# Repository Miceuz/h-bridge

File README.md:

h-bridge
========

High voltage H-bridge driver

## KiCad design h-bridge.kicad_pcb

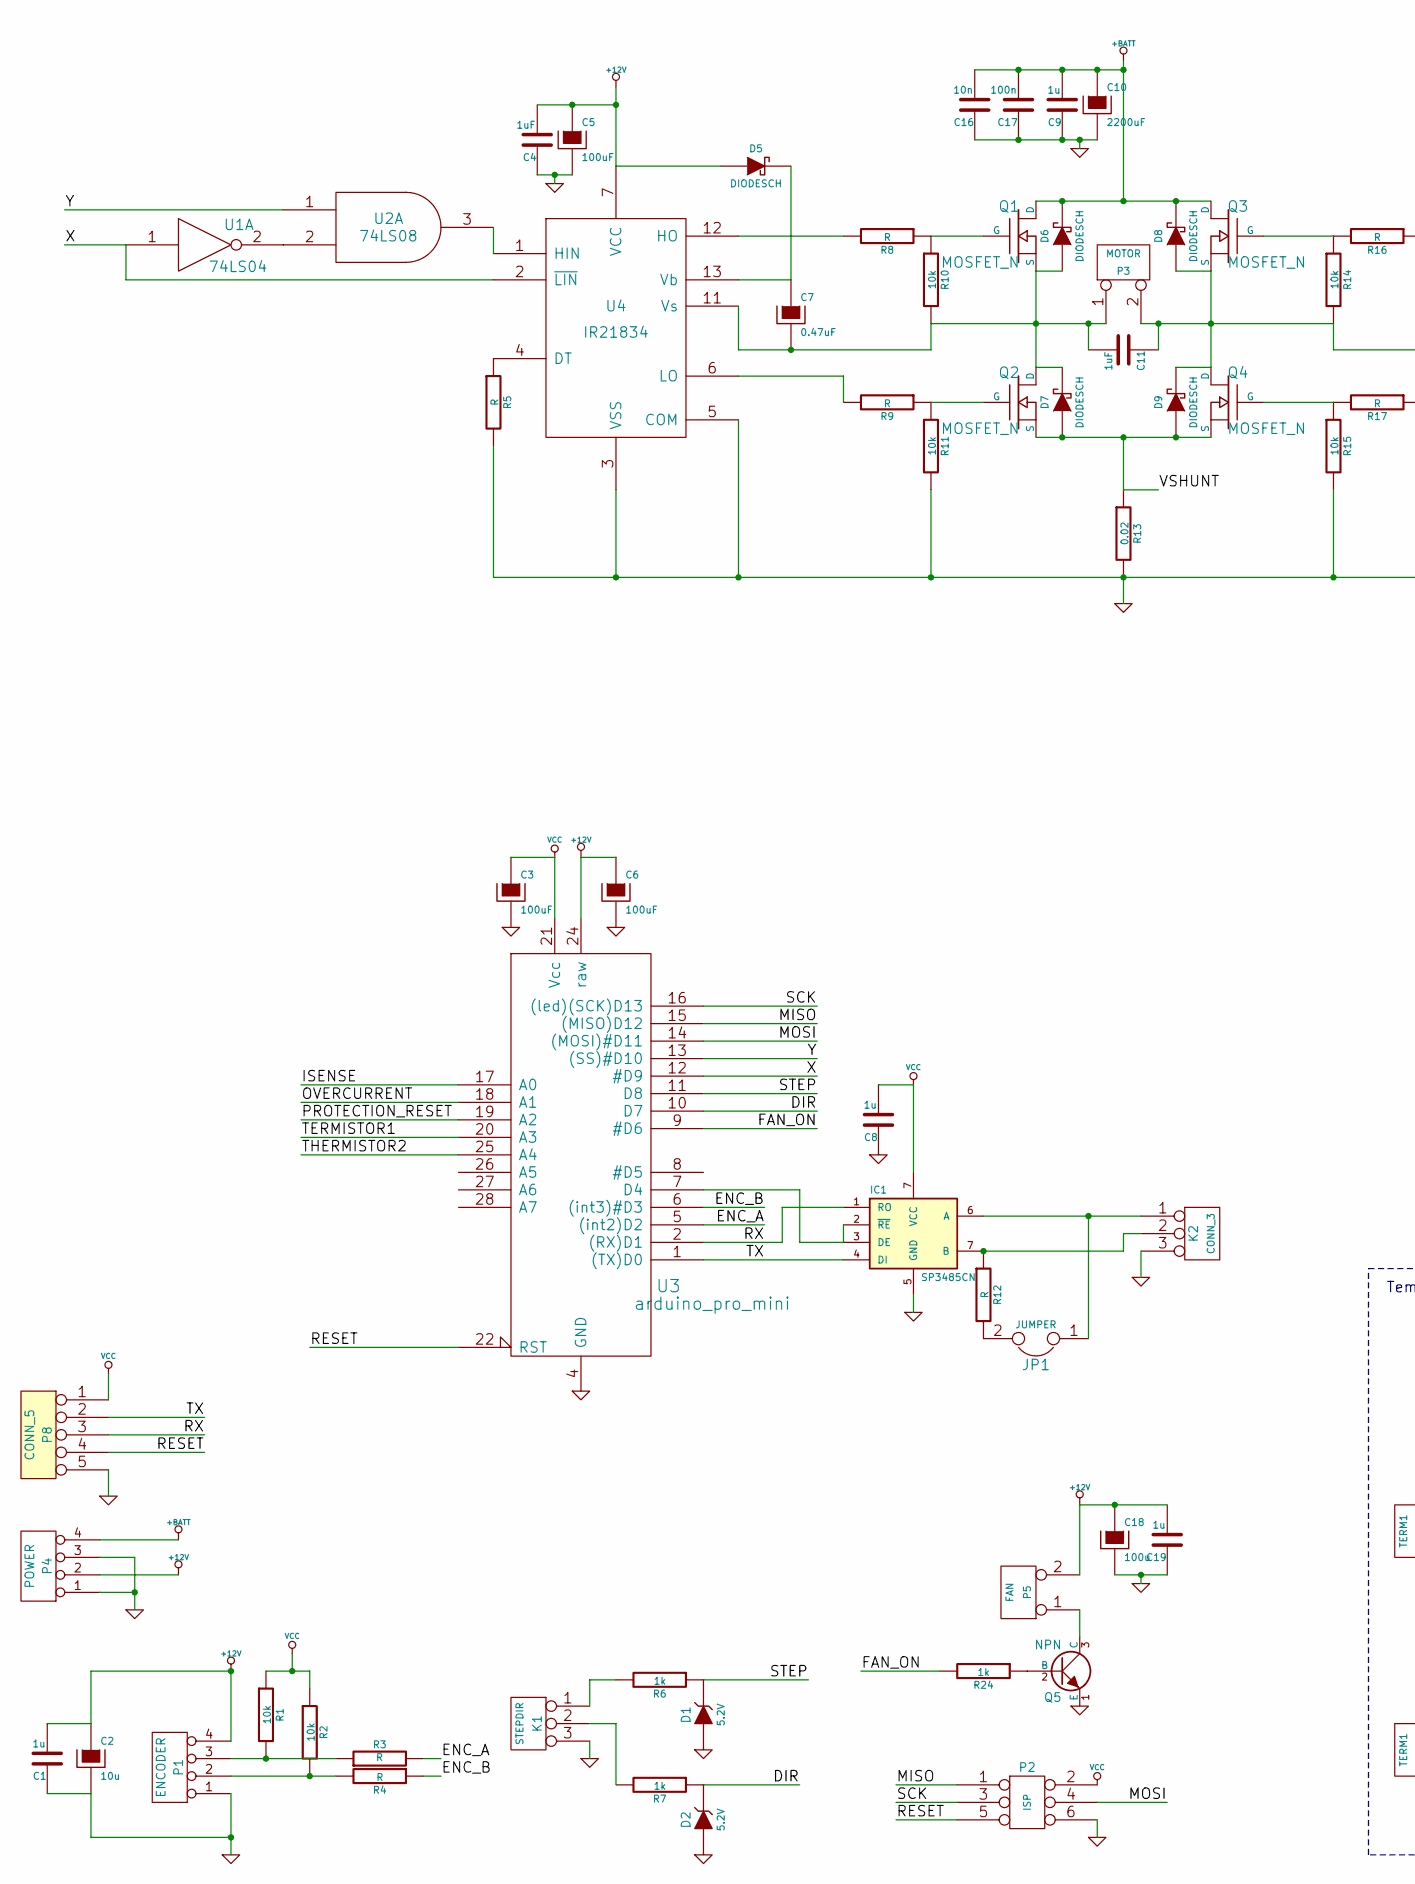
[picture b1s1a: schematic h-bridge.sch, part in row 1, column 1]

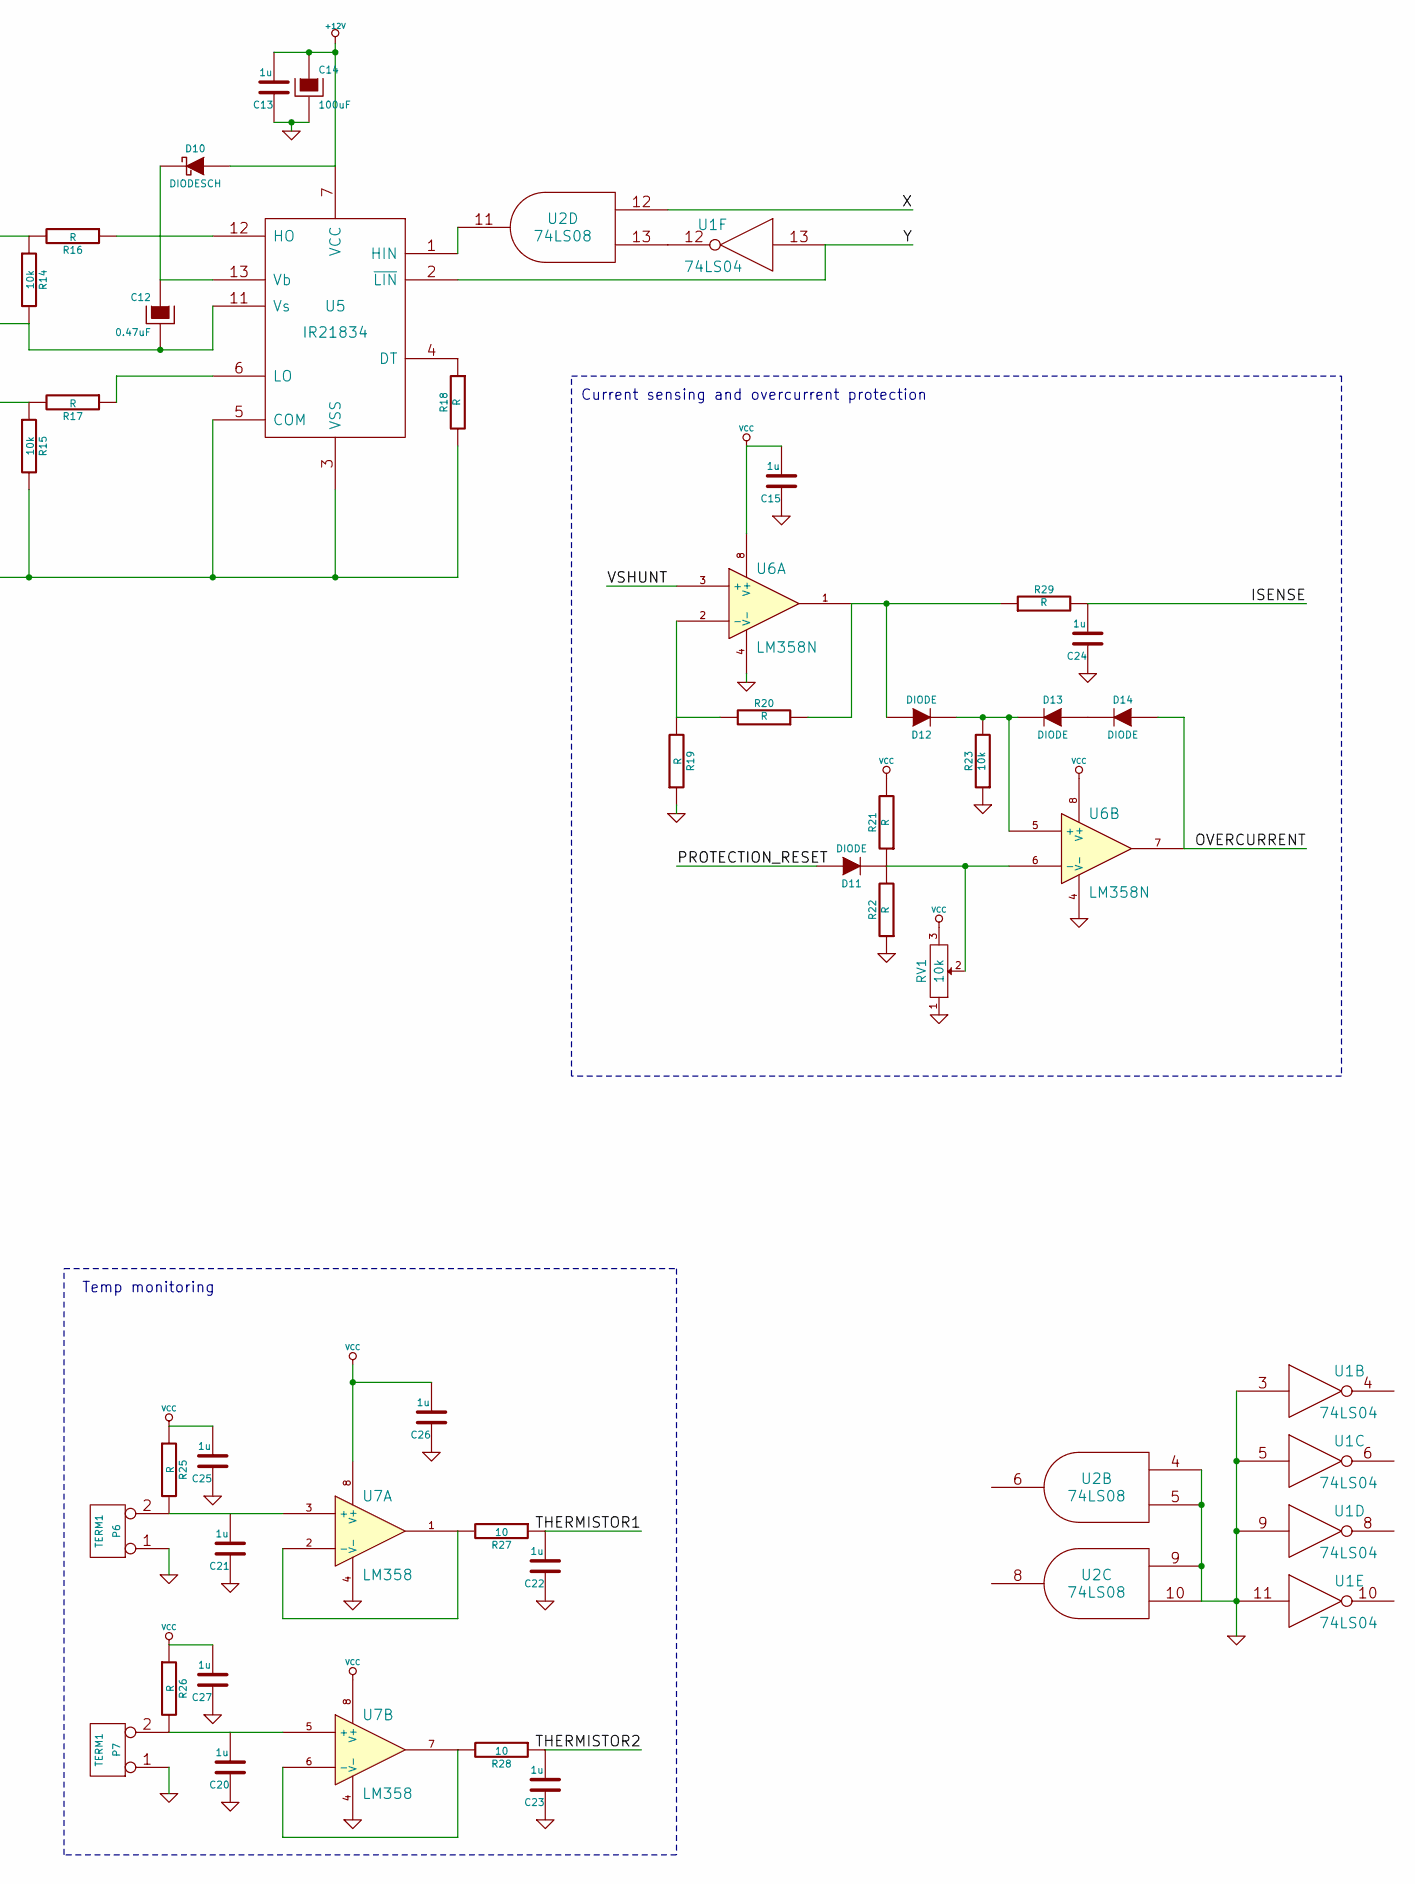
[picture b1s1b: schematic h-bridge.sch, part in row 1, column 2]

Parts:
C1, C8, C9, C13, C15, C19, C20, C21, C22, C23, C24, C26: 1u; SMD-0603_c
C2: 10u; Elko_vert_DM6-3_RM2-5_CopperClear
C3, C5, C6, C14: 100uF; Elko_vert_DM6-3_RM2-5_CopperClear
C4, C11: 1uF; SMD-0603_c
C7, C12: 0.47uF; Elko_vert_DM6-3_RM2-5_CopperClear
C10: 2200uF; Elko_vert_DM16_RM7-5_CopperClear
C16: 10n; SMD-0603_c
C17: 100n; SMD-0603_c
C18: 100u; Elko_vert_DM6-3_RM2-5_CopperClear
C25, C27: 1u
D1, D2: 5.2V
D5, D6, D7, D8, D9, D10: DIODESCH; Diode-SMA_Handsoldering
D11, D12, D13, D14: DIODE; Diode-SMA_Handsoldering
IC1: SP3485CN; SOIC-8-W
JP1: JUMPER; Pin_Header_Straight_1x02
K1: STEPDIR; PINHEAD1-3
K2: CONN_3; PINHEAD1-3
P1: ENCODER; bornier4
P2: ISP; Pin_Header_Straight_2x03
P3: MOTOR; SolderWirePad_2x_2-5mmDrill
P4: POWER; bornier4
P5: FAN; bornier2
P6, P7: TERM1; bornier2
P8: CONN_5
Q1, Q2, Q3, Q4: MOSFET_N; TO-220_FET-GDS_Vertical_LargePads
Q5: NPN; sot23
R1, R2, R10, R11, R14, R15, R23: 10k; SMD-0603_r
R3, R4, R5, R8, R9, R12, R16, R17, R18, R19, R20, R21, R22, R25, R26, R29: R; SMD-0603_r
R6, R7, R24: 1k; SMD-0603_r
R13: 0.02; Resistor_Ceramic_Horizontal_L65mm-W16mm-H15mm-p80mm
R27, R28: 10; SMD-0603_r
RV1: 10k; Potentiometer_Trimmer-Piher-PT15-h5_vertical
U1: 74LS04; SOIC-14_W
U2: 74LS08; SOIC-14_W
U3: arduino_pro_mini; ARDUINO_PRO_MINI
U4, U5: IR21834; DIP-14__300_ELL
U6: LM358N; SOIC-8-W
U7: LM358; SOIC-8-W

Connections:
+12V: C1.2, C2.1, C4.2, C5.1, C6.1, C13.2, C14.1, C18.1, C19.2, D5.1 (A), D10.1 (A), P1.4, P4.2, P5.2 (PM), U3.24 (raw), U4.7 (VCC), U5.7 (VCC)
+BATT: C9.2, C10.1, C16.2, C17.2, D6.2 (K), D8.2 (K), P4.4, Q1.D, Q3.D
/DIR: D2.2 (K), R7.1, U3.10 (D7)
/ENC_A: R3.2, U3.5 ((int2)D2)
/ENC_B: R4.1, U3.6 ((int3)#D3)
/FAN_ON: R24.2, U3.9 (#D6)
/ISENSE: C24.2, R29.2, U3.17 (A0)
/MISO: P2.1, U3.15 ((MISO)D12)
/MOSI: P2.4, U3.14 ((MOSI)#D11)
/OVERCURRENT: D14.1 (A), U3.18 (A1), U6.7
/PROTECTION_RESET: D11.1 (A), U3.19 (A2)
/RESET: P2.5, P8.4, U3.22 (RST)
/RX: IC1.1 (RO), P8.3, U3.2 ((RX)D1)
/SCK: P2.3, U3.16 ((led)(SCK)D13)
/STEP: D1.2 (K), R6.1, U3.11 (D8)
/TERMISTOR1: U3.20 (A3)
/THERMISTOR1: C22.2, R27.1
/THERMISTOR2: C23.2, R28.1, U3.25 (A4)
/TX: IC1.4 (DI), P8.2, U3.1 ((TX)D0)
/VSHUNT: D7.1 (A), D9.1 (A), Q2.S, Q4.S, R13.1, U6.3 (+)
/X: U1.1, U2.12, U3.12 (#D9), U4.2 (~LIN)
/Y: U1.13, U2.1, U3.13 ((SS)#D10), U5.2 (~LIN)
GND: C1.1, C2.2, C3.2, C4.1, C5.2, C6.2, C8.1, C9.1, C10.2, C13.1, C14.2, C15.1, C16.1, C17.1, C18.2, C19.1, C20.1, C21.1, C22.1, C23.1, C24.1, C25.1, C26.1, C27.1, D1.1 (A), D2.1 (A), IC1.5 (GND), K1.3, K2.3, P1.1, P2.6, P4.1, P4.3, P6.1, P7.1, P8.5, Q5.1 (E), R5.2, R11.2, R13.2, R15.2, R18.2, R19.1, R22.1, R23.1, RV1.1, U1.3, U1.5, U1.7 (GND), U1.9, U1.11, U2.4, U2.5, U2.7 (GND), U2.9, U2.10, U3.4 (GND), U3.23 (GND), U4.3 (VSS), U4.5 (COM), U5.3 (VSS), U5.5 (COM), U6.4 (V-), U7.4 (V-)
unnamed: C7.1, D5.2 (K), U4.13 (Vb)
unnamed: C11.1, C12.2, D8.1 (A), D9.2 (K), P3.2 (PM), Q3.S, Q4.D, R14.2, U5.11 (Vs)
unnamed: C7.2, C11.2, D6.1 (A), D7.2 (K), P3.1, Q1.S, Q2.D, R10.2, U4.11 (Vs)
unnamed: C12.1, D10.2 (K), U5.13 (Vb)
unnamed: D11.2 (K), R21.1, R22.2, RV1.2, U6.6 (-)
unnamed: D12.1 (A), R20.1, R29.1, U6.1
unnamed: D12.2 (K), D13.2 (K), R23.2, U6.5 (+)
unnamed: D13.1 (A), D14.2 (K)
unnamed: IC1.2 (~RE~), IC1.3 (DE), U3.7 (D4)
unnamed: IC1.6 (A), JP1.1, K2.1
unnamed: JP1.2, R12.2
unnamed: K1.1, R6.2
unnamed: K1.2 (PM), R7.2
unnamed: P1.2, R2.2, R4.2
unnamed: P1.3, R1.2, R3.1
unnamed: P5.1, Q5.3 (C)
unnamed: P6.2 (PM), R25.2, U7.3 (+)
unnamed: P7.2 (PM), R26.2, U7.5 (+)
unnamed: Q1.G, R8.1, R10.1
unnamed: Q2.G, R9.1, R11.1
unnamed: Q3.G, R14.1, R16.2
unnamed: Q4.G, R15.1, R17.2
unnamed: Q5.2 (B), R24.1
unnamed: R5.1, U4.4 (DT)
unnamed: R8.2, U4.12 (HO)
unnamed: R9.2, U4.6 (LO)
unnamed: R16.1, U5.12 (HO)
unnamed: R17.1, U5.6 (LO)
unnamed: R18.1, U5.4 (DT)
unnamed: R19.2, R20.2, U6.2 (-)
unnamed: R27.2, U7.1, U7.2 (-)
unnamed: R28.2, U7.6 (-), U7.7
unnamed: U1.2, U2.2
unnamed: U1.12, U2.13
unnamed: U2.3, U4.1 (HIN)
unnamed: U2.11, U5.1 (HIN)

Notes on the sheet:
Current sensing and overcurrent protection
Temp monitoring

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
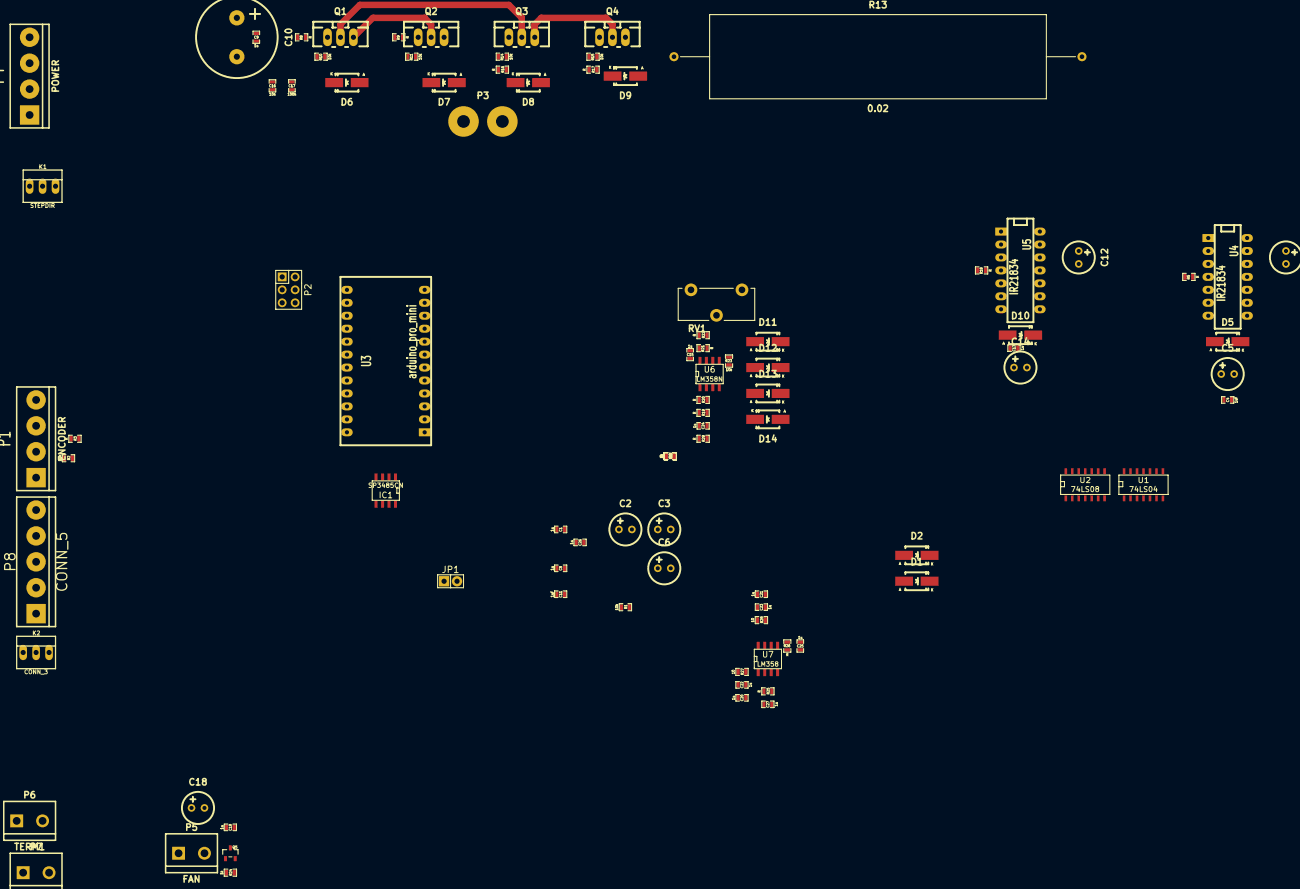
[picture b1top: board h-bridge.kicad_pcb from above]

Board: 2 copper layers, 93 parts (0 on the bottom side), 60 nets.

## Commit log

2014-11-22 initial
2014-11-22 add svg files
2014-11-22 test
